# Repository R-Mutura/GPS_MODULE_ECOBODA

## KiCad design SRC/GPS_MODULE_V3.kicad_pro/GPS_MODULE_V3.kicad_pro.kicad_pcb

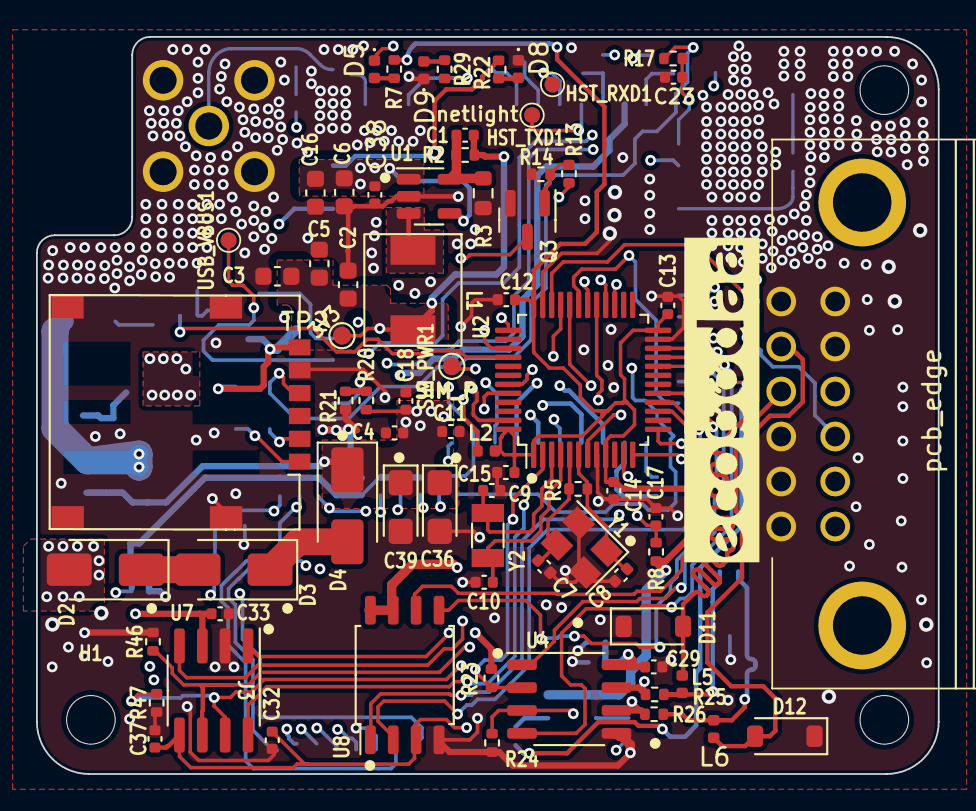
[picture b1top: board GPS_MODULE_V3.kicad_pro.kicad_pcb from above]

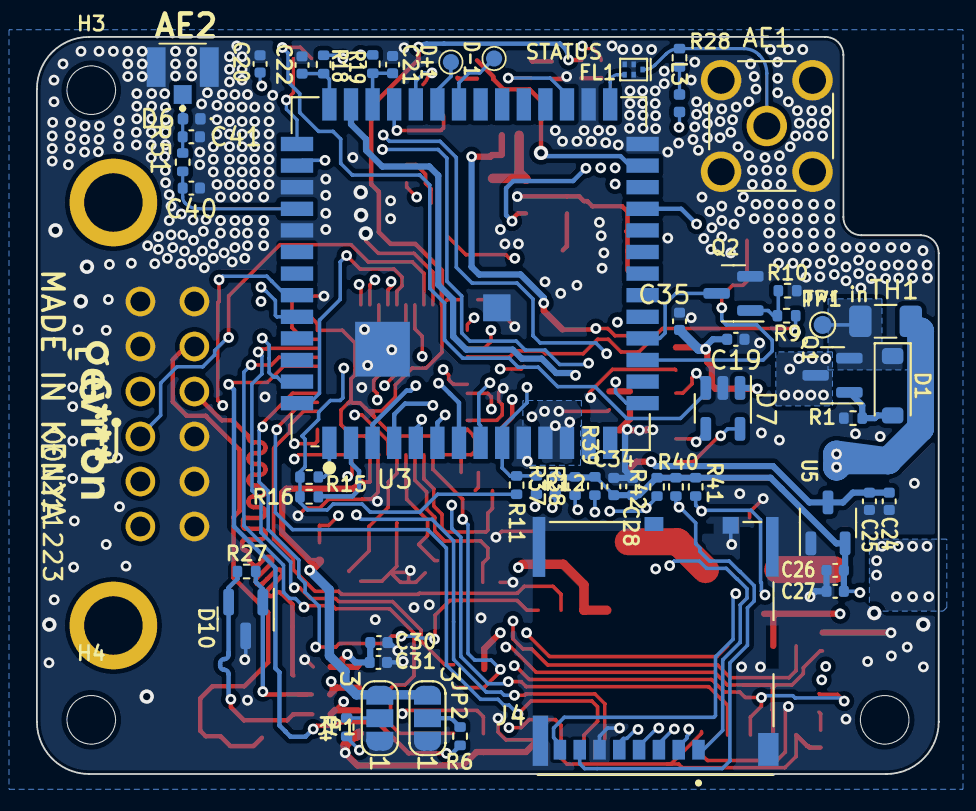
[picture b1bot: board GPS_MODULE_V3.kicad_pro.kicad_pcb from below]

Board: 4 copper layers, 50.1 x 41.0 mm, 128 parts (56 on the bottom side), 86 nets.

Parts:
AE1: Antenna_Shield; SMA_Molex_73251-2200_Horizontal
AE2: Antenna_Shield; UFL_COAX_CONN23370191
C1: 8.2p; C_0402_1005Metric
C2: 10n; C_0603_1608Metric
C3: 33p; C_0603_1608Metric
C4, C20, C25, C27, C34: 1u; C_0402_1005Metric
C5: 22u; C_0603_1608Metric
C6, C16: 10u; C_0603_1608Metric
C7, C8, C9, C10, C21, C22, C23: 22p; C_0402_1005Metric
C11, C18, C31: 10u; C_0402_1005Metric
C12, C13, C14, C15, C17, C29, C30, C32, C33, C35, C37, C38: 100n; C_0402_1005Metric
C19, C24, C26, C28: 0.1u; C_0402_1005Metric
C36, C39: 100u; CP_EIA-3216-18_Kemet-A
C40, C41: C_Small; C_0402_1005Metric
D1: MMSZ5232B-E3-08; D_SOD-123
D2, D3, D4: RS1K-E3/5AT; D_SMA
D5: LED; LED_0402_1005Metric
D6: LXES15AAA1-153; D_0402_1005Metric
D7: SP0504BAHT; SOT-23-5
D8: ORANGE; LED_0402_1005Metric
D9: BLUE; LED_0402_1005Metric
D10: ESDONCAN1LT1G; SOT-23
D11, D12: BEP0080MA; D_SOD-123
D+1: D+; TestPoint_Pad_D0.9mm
D-1: D-; TestPoint_Pad_D0.9mm
FL1: SAFEB1G57KE0F00R15; Filter_1411-5_1.4x1.1mm
H1, H3, H4: MountingHole; MountingHole_2.7mm
HST_RXD1: HST_RXD; TestPoint_Pad_D0.9mm
HST_TXD1: HST_TXD; TestPoint_Pad_D0.9mm
J3: nano_sim; nano_sim_NSIM-2-C
J4: Micro_SD_Card; MOLEX_503398-1892
J5: Conn_02x06_Counter_Clockwise; auto_jae_conn_02x06_p2.5mm_MX23A12NF1
JP1: BOOT0; SolderJumper-3_P1.3mm_Open_RoundedPad1.0x1.5mm_NumberLabels
JP2: BOOT1; SolderJumper-3_P1.3mm_Open_RoundedPad1.0x1.5mm_NumberLabels
L1: 2.2u; MDA5030-100M
L2, L5, L6: L_Ferrite; L_0402_1005Metric
L3: 82nH; L_0402_1005Metric
Q1: SSM3J328R-HXY; SOT-23
Q2, Q3: BSN20; SOT-23
R1: 1K; R_0402_1005Metric
R2: 180K; R_0402_1005Metric
R3: 40K; R_0603_1608Metric
R4, R6, R21, R23, R24: 100K; R_0402_1005Metric
R5: 1M; R_0402_1005Metric
R7: 499R; R_0402_1005Metric
R8, R10, R11, R14: 10K; R_0402_1005Metric
R9, R12, R13: 1k; R_0402_1005Metric
R15, R16: 2.2K; R_0402_1005Metric
R17, R18, R19, R28: 22R; R_0402_1005Metric
R20: 200K; R_0402_1005Metric
R22, R29: 390R; R_0402_1005Metric
R25, R26: 10R; R_0402_1005Metric
R27: 220R; R_0402_1005Metric
R37, R38, R39, R40, R41, R42: 10k; R_0402_1005Metric
R46, R47: 60R; R_0402_1005Metric
R51: 0R; R_0402_1005Metric
SIM_PWR1: TestPoint; TestPoint_Pad_D1.0mm
TH1: Thermistor_PTC; Fuse_1206_3216Metric
TP1, TP2: TestPoint; TestPoint_Pad_D1.0mm
U1: SY8089AAAC; SOT-23-5
U2: STM32F103C8Tx; LQFP-48_7x7mm_P0.5mm
U3: A9G_MODULE
U4: MAX485E; SOP-8_3.9x4.9mm_P1.27mm
U5: XC6206PxxxMR; SOT-23-3
U7: ATA6561-GAQW-N; SOIC-8_3.9x4.9mm_P1.27mm
U8: W25Q32JVSS; SOIC-8_5.23x5.23mm_P1.27mm
USB_VBUS1: USB_VBUS; TestPoint_Pad_D0.9mm
Y1: 8MHz; Crystal_SMD_3225-4Pin_3.2x2.5mm
Y2: 32.678KHz; Crystal_SMD_3215-2Pin_3.2x1.5mm

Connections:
2V8: C26.1, C27.1, C28.1, C34.1, J4.4 (VDD), R37.1, R38.1, R39.1, R40.1, R41.1, R42.1, U5.2 (VO)
4.2V_SIMPWR: C4.1, C11.1, C18.1, C24.1, C25.1, C36.1, C39.1, D4.1 (K), L3.2, R20.2, SIM_PWR1.1, U3.11 (VBAT), U3.12 (VBAT), U5.3 (VI)
+3V3: C1.1, C2.1, C3.1, C5.1, C29.1, C30.1, C31.1, C32.1, C37.1, L1.2, L2.1, R2.1, R23.2, TP2.1, U4.8 (VCC), U7.5 (NSIL), U8.3 (IO2), U8.7 (IO3), U8.8 (VCC)
+5V: C33.1, J5.12, TH1.1, U7.3 (VCC)
/5V_FILTERED_: C6.1, C16.1, C38.1, D2.2 (A), Q1.3 (D), U1.1 (EN), U1.4 (IN)
/A9G_GSM_GPRS_MODULE/GPRS_NET-STATUS: R22.1, U3.26 (IO27)
/A9G_GSM_GPRS_MODULE/GPS POSITION: R29.1, U3.30 (IO28)
/A9G_GSM_GPRS_MODULE/IO29: R12.1, U3.24 (IO29)
/A9G_GSM_GPRS_MODULE/PWRKEY: R13.1, U2.28 (PB15)
/A9G_GSM_GPRS_MODULE/Sim_CLK: C22.1, R18.1, U3.41 (SIM_CLK)
/A9G_GSM_GPRS_MODULE/Sim_DIO: C21.1, R19.1, U3.39 (SIM_DIO)
/A9G_GSM_GPRS_MODULE/Sim_RST: C23.1, R17.1, U3.42 (SIM_RST)
/A9G_GSM_GPRS_MODULE/Sim_Restart: R9.1, U2.40 (PB4)
/A9G_GSM_GPRS_MODULE/TF_CARD_CONN/SD_CLK: J4.5 (CLK), R42.2, U3.8 (SD_CLK/SPI1_CLK/I2C1_SCL/IO8)
/A9G_GSM_GPRS_MODULE/TF_CARD_CONN/SD_CMD: J4.3 (CMD), R39.2, U3.7 (SD_CMD/SPI1_SC0/I2C1_SDA/IO9)
/A9G_GSM_GPRS_MODULE/TF_CARD_CONN/SD_D0: J4.7 (DAT0), R40.2, U3.6 (SD_D0/SPI1_CSI/IO10)
/A9G_GSM_GPRS_MODULE/TF_CARD_CONN/SD_D1: J4.8 (DAT1), R41.2, U3.5 (SD_D1/SPI1_D0/IO11)
/A9G_GSM_GPRS_MODULE/TF_CARD_CONN/SD_D2: J4.1 (DAT2), R37.2, U3.4 (SD_D2/SPI1_DI/IO12)
/A9G_GSM_GPRS_MODULE/TF_CARD_CONN/SD_D3: J4.2 (DAT3/CD), R38.2, U3.3 (SD_D3/IO13)
/A9G_GSM_GPRS_MODULE/VIO: C20.1, R11.2, R15.2, R16.2, U3.43 (VIO)
/A9G_GSM_GPRS_MODULE/V_Sim: C19.2, C35.1, D7.1 (K), J3.C1 (VCC), U3.40 (VSIM)
/CAN_TRANSCEIVER_ATA6561/CAN_RX: U2.32 (PA11), U7.4 (RXD)
/CAN_TRANSCEIVER_ATA6561/CAN_STBY: U2.29 (PA8), U7.8 (STBY)
/CAN_TRANSCEIVER_ATA6561/CAN_TX: U2.33 (PA12), U7.1 (TXD)
/FLASH_MEMORY/CS: U2.11 (PA1), U8.1 (~CS)
/FLASH_MEMORY/MISO: U2.16 (PA6), U8.2 (DO(IO1))
/FLASH_MEMORY/MOSI: U2.17 (PA7), U8.5 (DI(IO0))
/FLASH_MEMORY/SCK: U2.15 (PA5), U8.6 (CLK)
/RS485_MAX485/A: D12.2 (A2), J5.2, L6.2
/RS485_MAX485/B: D11.2 (A2), J5.3, L5.2
/RS485_MAX485/RS485_DE: R24.2, U2.27 (PB14), U4.3 (DE)
/RS485_MAX485/RS485_~RE: R23.1, U2.2 (PC13), U4.2 (~RE)
/STM32F103C8T6_MCU/3v3_stm: C12.1, C13.1, C14.1, C15.1, JP1.3 (B), JP2.3 (B), L2.2, R7.1, R8.1, U2.1 (VBAT), U2.9 (VDDA), U2.24 (VDD), U2.36 (VDD), U2.48 (VDD)
/STM32F103C8T6_MCU/BOOT0: R4.1, U2.44 (BOOT0)
/STM32F103C8T6_MCU/BOOT1: R6.2, U2.20 (PB2)
/STM32F103C8T6_MCU/RX1: U2.31 (PA10), U3.54 (UART1_TXD/IO1)
/STM32F103C8T6_MCU/RX2: U2.13 (PA3), U3.49 (UART2_TXD/IO4)
/STM32F103C8T6_MCU/RX3: U2.22 (PB11), U4.1 (RO)
/STM32F103C8T6_MCU/SW0: J5.11, U2.39 (PB3)
/STM32F103C8T6_MCU/TX1: U2.30 (PA9), U3.53 (UART1_RXD/IO0)
/STM32F103C8T6_MCU/TX2: U2.12 (PA2), U3.50 (UART2_RXD/IO5)
/STM32F103C8T6_MCU/TX3: U2.21 (PB10), U4.4 (DI)
/STM32F103C8T6_MCU/mcu_reset: C17.1, R8.2, U2.7 (NRST)
/STM32F103C8T6_MCU/swdclk: J5.9, U2.37 (PA14)
/STM32F103C8T6_MCU/swdio: J5.10, U2.34 (PA13)
/STM32F103C8T6_MCU/xtal_1: C9.2, U2.3 (PC14), Y2.2
/STM32F103C8T6_MCU/xtal_2: C10.2, U2.4 (PC15), Y2.1
/STM32F103C8T6_MCU/xtal_in: C7.2, R5.1, U2.5 (PD0), Y1.3
/STM32F103C8T6_MCU/xtal_out: C8.2, R5.2, U2.6 (PD1), Y1.1
A_to_CANL: R26.1, R46.1, U4.6 (A), U7.6 (CANL)
B_to_CANH: R25.1, R47.1, U4.7 (B), U7.7 (CANH)
GND: AE1.2 (Shield), AE2.2 (Shield), C2.2, C3.2, C4.2, C5.2, C6.2, C7.1, C8.1, C9.1, C10.1, C11.2, C12.2, C13.2, C14.2, C15.2, C16.2, C17.2, C18.2, C19.1, C20.2, C21.2, C22.2, C23.2, C24.2, C25.2, C26.2, C27.2, C28.2, C29.2, C30.2, C31.2, C32.2, C33.2, C34.2, C35.2, C36.2, C37.2, C38.2, C39.2, C40.1, C41.1, D6.1 (A1), D7.2 (A), D8.1 (K), D9.1 (K), D10.3 (A), D11.1 (A1), D12.1 (A1), FL1.2, FL1.3, FL1.5, J3.C5 (GND), J3.MP1, J4.6 (VSS), J4.9 (SHIELD), J5.1, J5.4, J5.5, J5.6, J5.7, J5.8, JP1.1 (A), JP2.1 (A), Q2.2 (S), Q3.2 (S), R1.2, R3.2, R10.1, R14.1, R21.1, R24.1, R46.2, R47.2, U1.2 (GND), U2.8 (VSSA), U2.23 (VSS), U2.35 (VSS), U2.47 (VSS), U3.10 (GND), U3.27 (GND), U3.29 (GND), U3.44 (GND), U3.46 (GND), U3.55 (GND), U3.56 (GND), U4.5 (GND), U5.1 (GND), U7.2 (GND), U8.4 (GND), Y1.2, Y1.4
unnamed: AE1.1 (A), FL1.1, R28.2
unnamed: AE2.1 (A), C41.2, D6.2 (A2), R51.2
unnamed: D1.2 (A), Q1.1 (G), R1.1
unnamed: D1.1 (K), Q1.2 (S), TH1.2, TP1.1
unnamed: D2.1 (K), D3.2 (A)
unnamed: D3.1 (K), D4.2 (A)
unnamed: D5.2 (A), R7.2
unnamed: D5.1 (K), U2.43 (PB7)
unnamed: D8.2 (A), R22.2
unnamed: D9.2 (A), R29.2
unnamed: D10.1 (K), L5.1, R25.2, R27.2
unnamed: D10.2 (K), L6.1, R26.2, R27.1
unnamed: D7.4 (K), J3.C3 (CLK), R18.2
unnamed: D7.5 (K), J3.C7 (I/O), R19.2
unnamed: D7.3 (K), J3.C2 (RST), R17.2
unnamed: JP1.2 (C), R4.2
unnamed: JP2.2 (C), R6.1
unnamed: L3.1, R28.1
unnamed: Q2.3 (D), U3.18 (RESET)
unnamed: Q2.1 (G), R9.2, R10.2
unnamed: Q3.3 (D), R11.1, R12.2, U3.9 (PWR_KEY)
unnamed: Q3.1 (G), R13.2, R14.2
unnamed: C1.2, R2.2, R3.1, U1.5 (FB)
unnamed: L1.1, U1.3 (LX)
unnamed: R20.1, R21.2, U3.15 (ADC0)
unnamed: FL1.4, U3.28 (GPS_RF)
unnamed: C40.2, R51.1, U3.45 (GSM_RF)
unnamed: HST_TXD1.1, U3.38 (HST_RXD)
unnamed: HST_RXD1.1, U3.37 (HST_TXD)
unnamed: R15.1, U3.1 (I2C2_SCL/IO19)
unnamed: R16.1, U3.2 (I2C2_SDA/IO20)
unnamed: D-1.1, U3.35 (USB_N)
unnamed: D+1.1, U3.36 (USB_P)
unnamed: U3.17 (VUSB_DET), USB_VBUS1.1

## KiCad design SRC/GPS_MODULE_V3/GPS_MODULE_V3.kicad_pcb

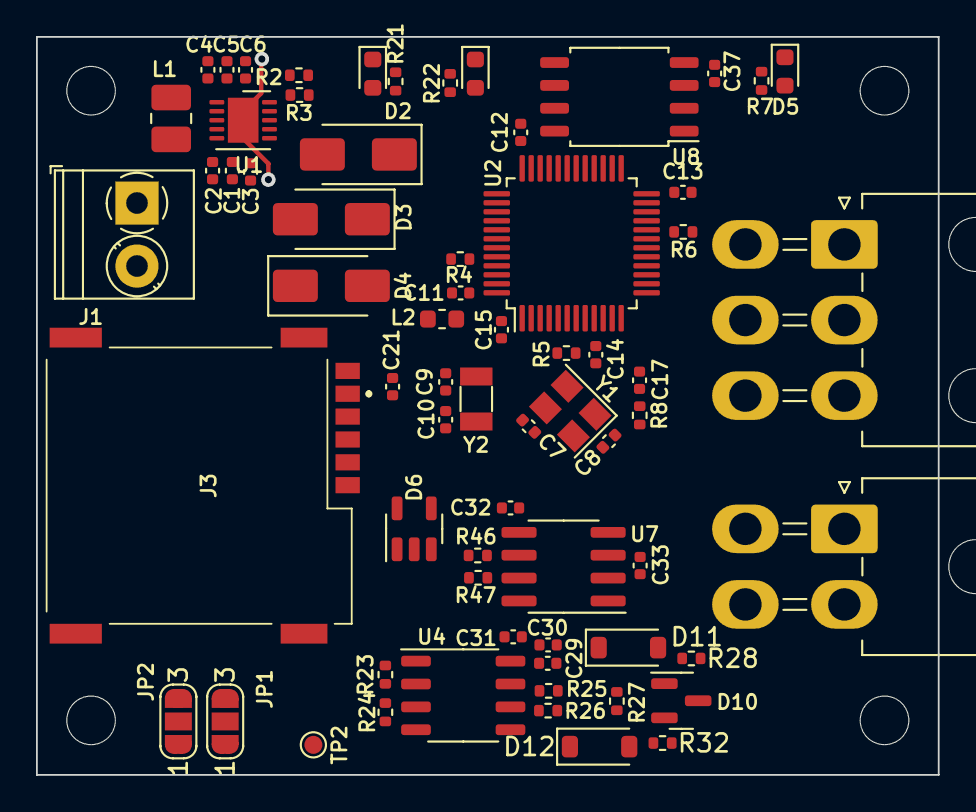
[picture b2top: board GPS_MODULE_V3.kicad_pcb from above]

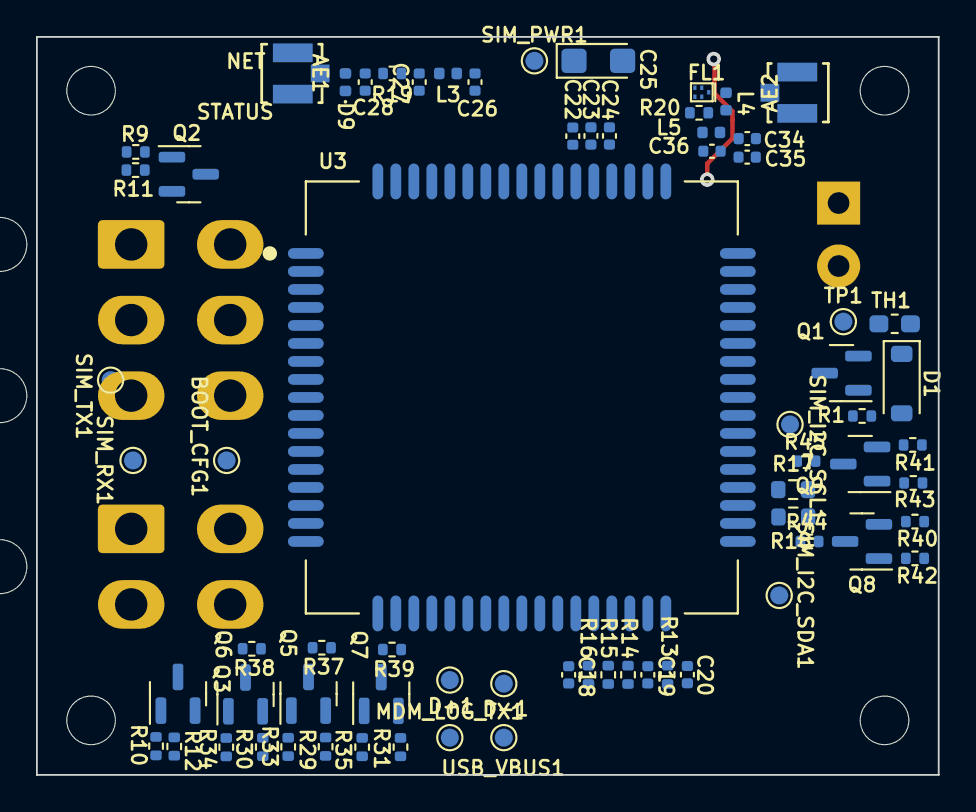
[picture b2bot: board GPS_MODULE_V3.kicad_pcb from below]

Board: 2 copper layers, 50.1 x 41.0 mm, 141 parts (70 on the bottom side), 91 nets.

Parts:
AE1, AE2: Antenna_Shield; CONN_2337019-1
BOOT_CFG1: BOOT_CFG; TestPoint_Pad_D1.0mm
C1, C3, C4, C6, C23, C24, C31: 10u; C_0402_1005Metric
C2, C5, C11, C12, C13, C14, C15, C17, C21, C29, C30, C32, C33, C37: 100n; C_0402_1005Metric
C7, C8, C9, C10, C18, C19, C20: 22p; C_0402_1005Metric
C22, C34: 1u; C_0402_1005Metric
C25: 100u; CP_EIA-3216-18_Kemet-A
C26: 0.3p; C_0402_1005Metric
C27, C28: C_0402_1005Metric
C35: 10n; C_0402_1005Metric
C36: 1n; C_0402_1005Metric
D1: MMSZ5232B-E3-08; D_SOD-123
D2, D3, D4: SS310; D_SMA
D5: LED; LED_0603_1608Metric
D6: SP0504BAHT; SOT-23-5
D7: ORANGE; LED_0603_1608Metric
D8: BLUE; LED_0603_1608Metric
D9: LXES15AAA1-153; D_0402_1005Metric
D10: ESDONCAN1LT1G; SOT-23
D11, D12: BEP0080MA; D_SOD-123
D+1: D+; TestPoint_Pad_D1.0mm
D-1: D-; TestPoint_Pad_D1.0mm
FL1: B39162B8813P810; Filter_1109-5_1.1x0.9mm
H1, H2, H3, H4: MountingHole; MountingHole_2.7mm
J1: Input; TerminalBlock_Phoenix_PT-1,5-2-3.5-H_1x02_P3.50mm_Horizontal
J2: Conn_02x02_Odd_Even; Molex_Mini-Fit_Jr_5569-04A2_2x02_P4.20mm_Horizontal
J3: Micro_Sim_card; SMC2026
J5: Conn_02x03_Odd_Even; Molex_Mini-Fit_Jr_5569-06A2_2x03_P4.20mm_Horizontal
JP1: BOOT0; SolderJumper-3_P1.3mm_Open_RoundedPad1.0x1.5mm_NumberLabels
JP2: BOOT1; SolderJumper-3_P1.3mm_Open_RoundedPad1.0x1.5mm_NumberLabels
L1: 1.5uH; L_1008_2520Metric_Pad1.43x2.20mm_HandSolder
L2: L_Ferrite; L_0603_1608Metric
L3: 1uH; L_0402_1005Metric
L4: 27nH; L_0402_1005Metric
L5: 100mHz 150/200R; L_0402_1005Metric
MDM_LOG_TX1: MDM_LOG_TX; TestPoint_Pad_D1.0mm
Q1: SSM3J328R-HXY; SOT-23
Q2, Q3: BSN20; SOT-23
Q5, Q6, Q7, Q8, Q9: 2N7002; SOT-23
R1, R2, R3, R29, R30, R31, R40, R41: 1K; R_0402_1005Metric
R4, R6, R23, R24: 100K; R_0402_1005Metric
R5: 1M; R_0402_1005Metric
R7: 499R; R_0402_1005Metric
R8, R11, R12, R16, R33, R34, R35, R37, R38, R39, R42, R43, R44, R45: 10K; R_0402_1005Metric
R9, R10: 1k; R_0402_1005Metric
R13, R14, R15: 22R; R_0402_1005Metric
R17, R18: 2.2K; R_0603_1608Metric
R19, R28, R32: 0R; R_0402_1005Metric
R20, R25, R26: 10R; R_0402_1005Metric
R21, R22: 390R; R_0402_1005Metric
R27: 220R; R_0402_1005Metric
R46, R47: 60R; R_0402_1005Metric
SIM_I2C_SCL1: SIM_I2C_SCL; TestPoint_Pad_D1.0mm
SIM_I2C_SDA1: SIM_I2C_SDA; TestPoint_Pad_D1.0mm
SIM_PWR1: TestPoint; TestPoint_Pad_D1.0mm
SIM_RX1: Sim_RX; TestPoint_Pad_D1.0mm
SIM_TX1: Sim_TX; TestPoint_Pad_D1.0mm
TH1: Thermistor_PTC; Fuse_0603_1608Metric_Pad1.05x0.95mm_HandSolder
TP1, TP2: TestPoint; TestPoint_Pad_D1.0mm
U1: ADP2504ACPZ-R7_3.3V_VERSION; DFN-10-1EP_3x3mm_P0.5mm_EP1.7x2.5mm
U2: STM32F103C8Tx; LQFP-48_7x7mm_P0.5mm
U3: SIM7000E; SIMCON_SIM7000E
U4: MAX485E; SOP-8_3.9x4.9mm_P1.27mm
U7: ATA6561-GAQW-N; SOIC-8_3.9x4.9mm_P1.27mm
U8: W25Q32JVSS; SOIC-8_5.23x5.23mm_P1.27mm
USB_VBUS1: USB_VBUS; TestPoint_Pad_D1.0mm
Y1: 8MHz; Crystal_SMD_3225-4Pin_3.2x2.5mm
Y2: 32.678KHz; Crystal_SMD_3215-2Pin_3.2x1.5mm

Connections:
4.2V_SIMPWR: C22.1, C23.1, C24.1, C25.1, D4.1 (K), SIM_PWR1.1, U3.55 (VBAT), U3.56 (VBAT), U3.57 (VBAT)
+3V3: C4.1, C5.1, C6.1, C29.1, C30.1, C31.1, C32.1, C34.1, C35.1, C37.1, L2.1, L5.1, R2.1, R23.2, R37.1, R38.1, R39.1, R44.1, R45.1, TP2.1, U1.1 (VOUT), U4.8 (VCC), U7.5 (NSIL), U8.3 (IO2), U8.7 (IO3), U8.8 (VCC)
+5V: C1.1, C2.1, C3.1, C33.1, D2.2 (A), J2.2, Q1.3 (D), U1.5 (PVIN), U1.6 (EN), U1.8 (VIN), U7.3 (VCC)
/CAN_TRANSCEIVER_ATA6561/CAN_RX: U2.33 (PA12), U7.4 (RXD)
/CAN_TRANSCEIVER_ATA6561/CAN_STBY: U2.29 (PA8), U7.8 (STBY)
/CAN_TRANSCEIVER_ATA6561/CAN_TX: U2.32 (PA11), U7.1 (TXD)
/FLASH_MEMORY/CS: U2.11 (PA1), U8.1 (~CS)
/FLASH_MEMORY/MISO: U2.16 (PA6), U8.2 (DO(IO1))
/FLASH_MEMORY/MOSI: U2.17 (PA7), U8.5 (DI(IO0))
/FLASH_MEMORY/SCK: U2.15 (PA5), U8.6 (CLK)
/RS485_MAX485/A: D12.2 (A2), J2.1, R32.2
/RS485_MAX485/B: D11.2 (A2), J2.3, R28.2
/RS485_MAX485/RS485_DE: R24.2, U2.27 (PB14), U4.3 (DE)
/RS485_MAX485/RS485_~RE: R23.1, U2.2 (PC13), U4.2 (~RE)
/SIM7000E_GPRS_SIM MODULE/GNSS_ANT: FL1.4, U3.53 (GNSS_ANT)
/SIM7000E_GPRS_SIM MODULE/GPS_RXD_: R40.1, U3.49 (GPIO1)
/SIM7000E_GPRS_SIM MODULE/GPS_TXD_: R41.1, U3.50 (GPIO0)
/SIM7000E_GPRS_SIM MODULE/MOSFET_LOGIC_LEVEL_TRANSLATOR/LOW_SIDE_SIM_DTR_LOGIC: R30.1, U3.3 (DTR)
/SIM7000E_GPRS_SIM MODULE/MOSFET_LOGIC_LEVEL_TRANSLATOR/LOW_SIDE_SIM_RXD_LOGIC: R29.1, U3.10 (RXD)
/SIM7000E_GPRS_SIM MODULE/MOSFET_LOGIC_LEVEL_TRANSLATOR/LOW_SIDE_SIM_TXD_LOGIC: R31.1, U3.9 (TXD)
/SIM7000E_GPRS_SIM MODULE/NETLIGHT: R21.1, U3.52 (NETLIGHT)
/SIM7000E_GPRS_SIM MODULE/PWRKEY: R9.1, U2.28 (PB15)
/SIM7000E_GPRS_SIM MODULE/RF_ANT: C26.2, L3.1, U3.60 (RF_ANT)
/SIM7000E_GPRS_SIM MODULE/SIM_DTR: Q6.3 (D), R38.2, U2.41 (PB5)
/SIM7000E_GPRS_SIM MODULE/STATUS: R22.1, U3.66 (STATUS)
/SIM7000E_GPRS_SIM MODULE/Sim_CLK: C19.1, R14.1, U3.32 (SIM_CLK)
/SIM7000E_GPRS_SIM MODULE/Sim_DIO: C18.1, R15.1, R16.1, U3.31 (SIM_DATA)
/SIM7000E_GPRS_SIM MODULE/Sim_RST: C20.1, R13.1, U3.33 (SIM_RST)
/SIM7000E_GPRS_SIM MODULE/Sim_Reset: R10.1, U2.40 (PB4)
/SIM7000E_GPRS_SIM MODULE/VDD_EXT: Q5.1 (G), Q6.1 (G), Q7.1 (G), Q8.1 (G), Q9.1 (G), R17.2, R18.2, R33.1, R34.1, R35.1, R42.1, R43.1, U3.15 (VDD_EXT)
/SIM7000E_GPRS_SIM MODULE/V_Sim: C21.1, D6.1 (K), J3.C1 (VCC), R16.2, U3.30 (SIM_VDD)
/SIM7000E_GPRS_SIM MODULE/gps_VDD: C36.1, L5.2, R20.2
/STM32F103C8T6_MCU/3v3_stm: C11.1, C12.1, C13.1, C14.1, C15.1, JP1.3 (B), JP2.3 (B), L2.2, R7.1, R8.1, U2.1 (VBAT), U2.9 (VDDA), U2.24 (VDD), U2.36 (VDD), U2.48 (VDD)
/STM32F103C8T6_MCU/BOOT0: R4.1, U2.44 (BOOT0)
/STM32F103C8T6_MCU/BOOT1: R6.2, U2.20 (PB2)
/STM32F103C8T6_MCU/RX1: Q7.3 (D), R39.2, SIM_RX1.1, U2.31 (PA10)
/STM32F103C8T6_MCU/RX2: Q9.3 (D), R45.2, U2.13 (PA3)
/STM32F103C8T6_MCU/RX3: U2.22 (PB11), U4.4 (DI)
/STM32F103C8T6_MCU/SW0: J5.2, U2.39 (PB3)
/STM32F103C8T6_MCU/TX1: Q5.3 (D), R37.2, SIM_TX1.1, U2.30 (PA9)
/STM32F103C8T6_MCU/TX2: Q8.3 (D), R44.2, U2.12 (PA2)
/STM32F103C8T6_MCU/TX3: U2.21 (PB10), U4.1 (RO)
/STM32F103C8T6_MCU/mcu_reset: C17.1, J5.4, R8.2, U2.7 (NRST)
/STM32F103C8T6_MCU/swdclk: J5.3, U2.37 (PA14)
/STM32F103C8T6_MCU/swdio: J5.1, U2.34 (PA13)
/STM32F103C8T6_MCU/xtal_1: C9.2, U2.3 (PC14), Y2.2
/STM32F103C8T6_MCU/xtal_2: C10.2, U2.4 (PC15), Y2.1
/STM32F103C8T6_MCU/xtal_in: C7.2, R5.1, U2.5 (PD0), Y1.3
/STM32F103C8T6_MCU/xtal_out: C8.2, R5.2, U2.6 (PD1), Y1.1
A_to_CANL: R26.1, R46.1, U4.6 (A), U7.6 (CANL)
B_to_CANH: R25.1, R47.1, U4.7 (B), U7.7 (CANH)
GND: AE1.2 (Shield), AE2.2 (Shield), C1.2, C2.2, C3.2, C4.2, C5.2, C6.2, C7.1, C8.1, C9.1, C10.1, C11.2, C12.2, C13.2, C14.2, C15.2, C17.2, C18.2, C19.2, C20.2, C21.2, C22.2, C23.2, C24.2, C25.2, C26.1, C27.1, C28.1, C29.2, C30.2, C31.2, C32.2, C33.2, C34.2, C35.2, C36.2, C37.2, D6.2 (A), D7.1 (K), D8.1 (K), D9.1 (A1), D10.3 (A), D11.1 (A1), D12.1 (A1), FL1.2, FL1.3, FL1.5, J1.2, J2.4, J3.C5 (GND), J3.MP1, J3.MP2, J3.MP3, J3.MP4, J5.5, J5.6, JP1.1 (A), JP2.1 (A), Q2.2 (S), Q3.2 (S), R1.2, R3.2, R11.1, R12.1, R24.1, R46.2, R47.2, U1.3 (PGND), U1.7 (SYNC), U1.9 (AGND), U2.8 (VSSA), U2.23 (VSS), U2.35 (VSS), U2.47 (VSS), U3.2 (GND), U3.17 (GND), U3.18 (GND), U3.29 (GND), U3.39 (GND), U3.45 (GND), U3.46 (GND), U3.54 (GND), U3.58 (GND), U3.59 (GND), U3.61 (GND), U3.62 (GND), U3.63 (GND), U3.64 (GND), U3.65 (GND), U4.5 (GND), U7.2 (GND), U8.4 (GND), Y1.2, Y1.4
unnamed: AE1.1 (A), C28.2, D9.2 (A2), R19.2
unnamed: AE2.1 (A), FL1.1, L4.2
unnamed: C27.2, L3.2, R19.1
unnamed: D1.2 (A), Q1.1 (G), R1.1
unnamed: D1.1 (K), Q1.2 (S), TH1.2, TP1.1
unnamed: D2.1 (K), D3.2 (A)
unnamed: D3.1 (K), D4.2 (A)
unnamed: D5.2 (A), R7.2
unnamed: D5.1 (K), U2.43 (PB7)
unnamed: D7.2 (A), R21.2
unnamed: D8.2 (A), R22.2
unnamed: D10.1 (K), R25.2, R27.2, R28.1
unnamed: D10.2 (K), R26.2, R27.1, R32.1
unnamed: J1.1, TH1.1
unnamed: D6.4 (K), J3.C3 (CLK), R14.2
unnamed: D6.5 (K), J3.C7 (I/O), R15.2
unnamed: D6.3 (K), J3.C2 (RST), R13.2
unnamed: JP1.2 (C), R4.2
unnamed: JP2.2 (C), R6.1
unnamed: L4.1, R20.1
unnamed: Q2.3 (D), U3.1 (~PWRKEY)
unnamed: Q2.1 (G), R9.2, R11.2
unnamed: Q3.3 (D), U3.16 (~NRESET)
unnamed: Q3.1 (G), R10.2, R12.2
unnamed: Q5.2 (S), R29.2, R33.2
unnamed: Q6.2 (S), R30.2, R34.2
unnamed: Q7.2 (S), R31.2, R35.2
unnamed: Q8.2 (S), R40.2, R42.2
unnamed: Q9.2 (S), R41.2, R43.2
unnamed: R2.2, R3.1, U1.10 (FB)
unnamed: L1.1, U1.4 (SW1)
unnamed: L1.2, U1.2 (SW2)
unnamed: BOOT_CFG1.1, U3.6 (BOOT_CFG)
unnamed: R17.1, SIM_I2C_SCL1.1, U3.38 (I2C_SCL)
unnamed: R18.1, SIM_I2C_SDA1.1, U3.37 (I2C_SDA)
unnamed: MDM_LOG_TX1.1, U3.23 (MDM_LOG_TX)
unnamed: D-1.1, U3.28 (USB_DM)
unnamed: D+1.1, U3.27 (USB_DP)
unnamed: U3.24 (USB_VBUS), USB_VBUS1.1

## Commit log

2023-12-10 layut completed
2023-12-10 images
2023-12-12 all items updated production ready
2023-12-12 added logo
2023-12-12 gps update on buck 3v3
2023-12-12 BOM updates
2024-01-16 updates on BOM, CPL and gerbers
2024-01-19 routing
2024-01-19 completed GPS
2024-01-20 fiducial, resistor and markings
2024-01-23 completed GPS ecoboda files
2024-01-23 update removal of all level shifts diodes
2024-02-07 GPS all files BOM and placemnt guide files added
